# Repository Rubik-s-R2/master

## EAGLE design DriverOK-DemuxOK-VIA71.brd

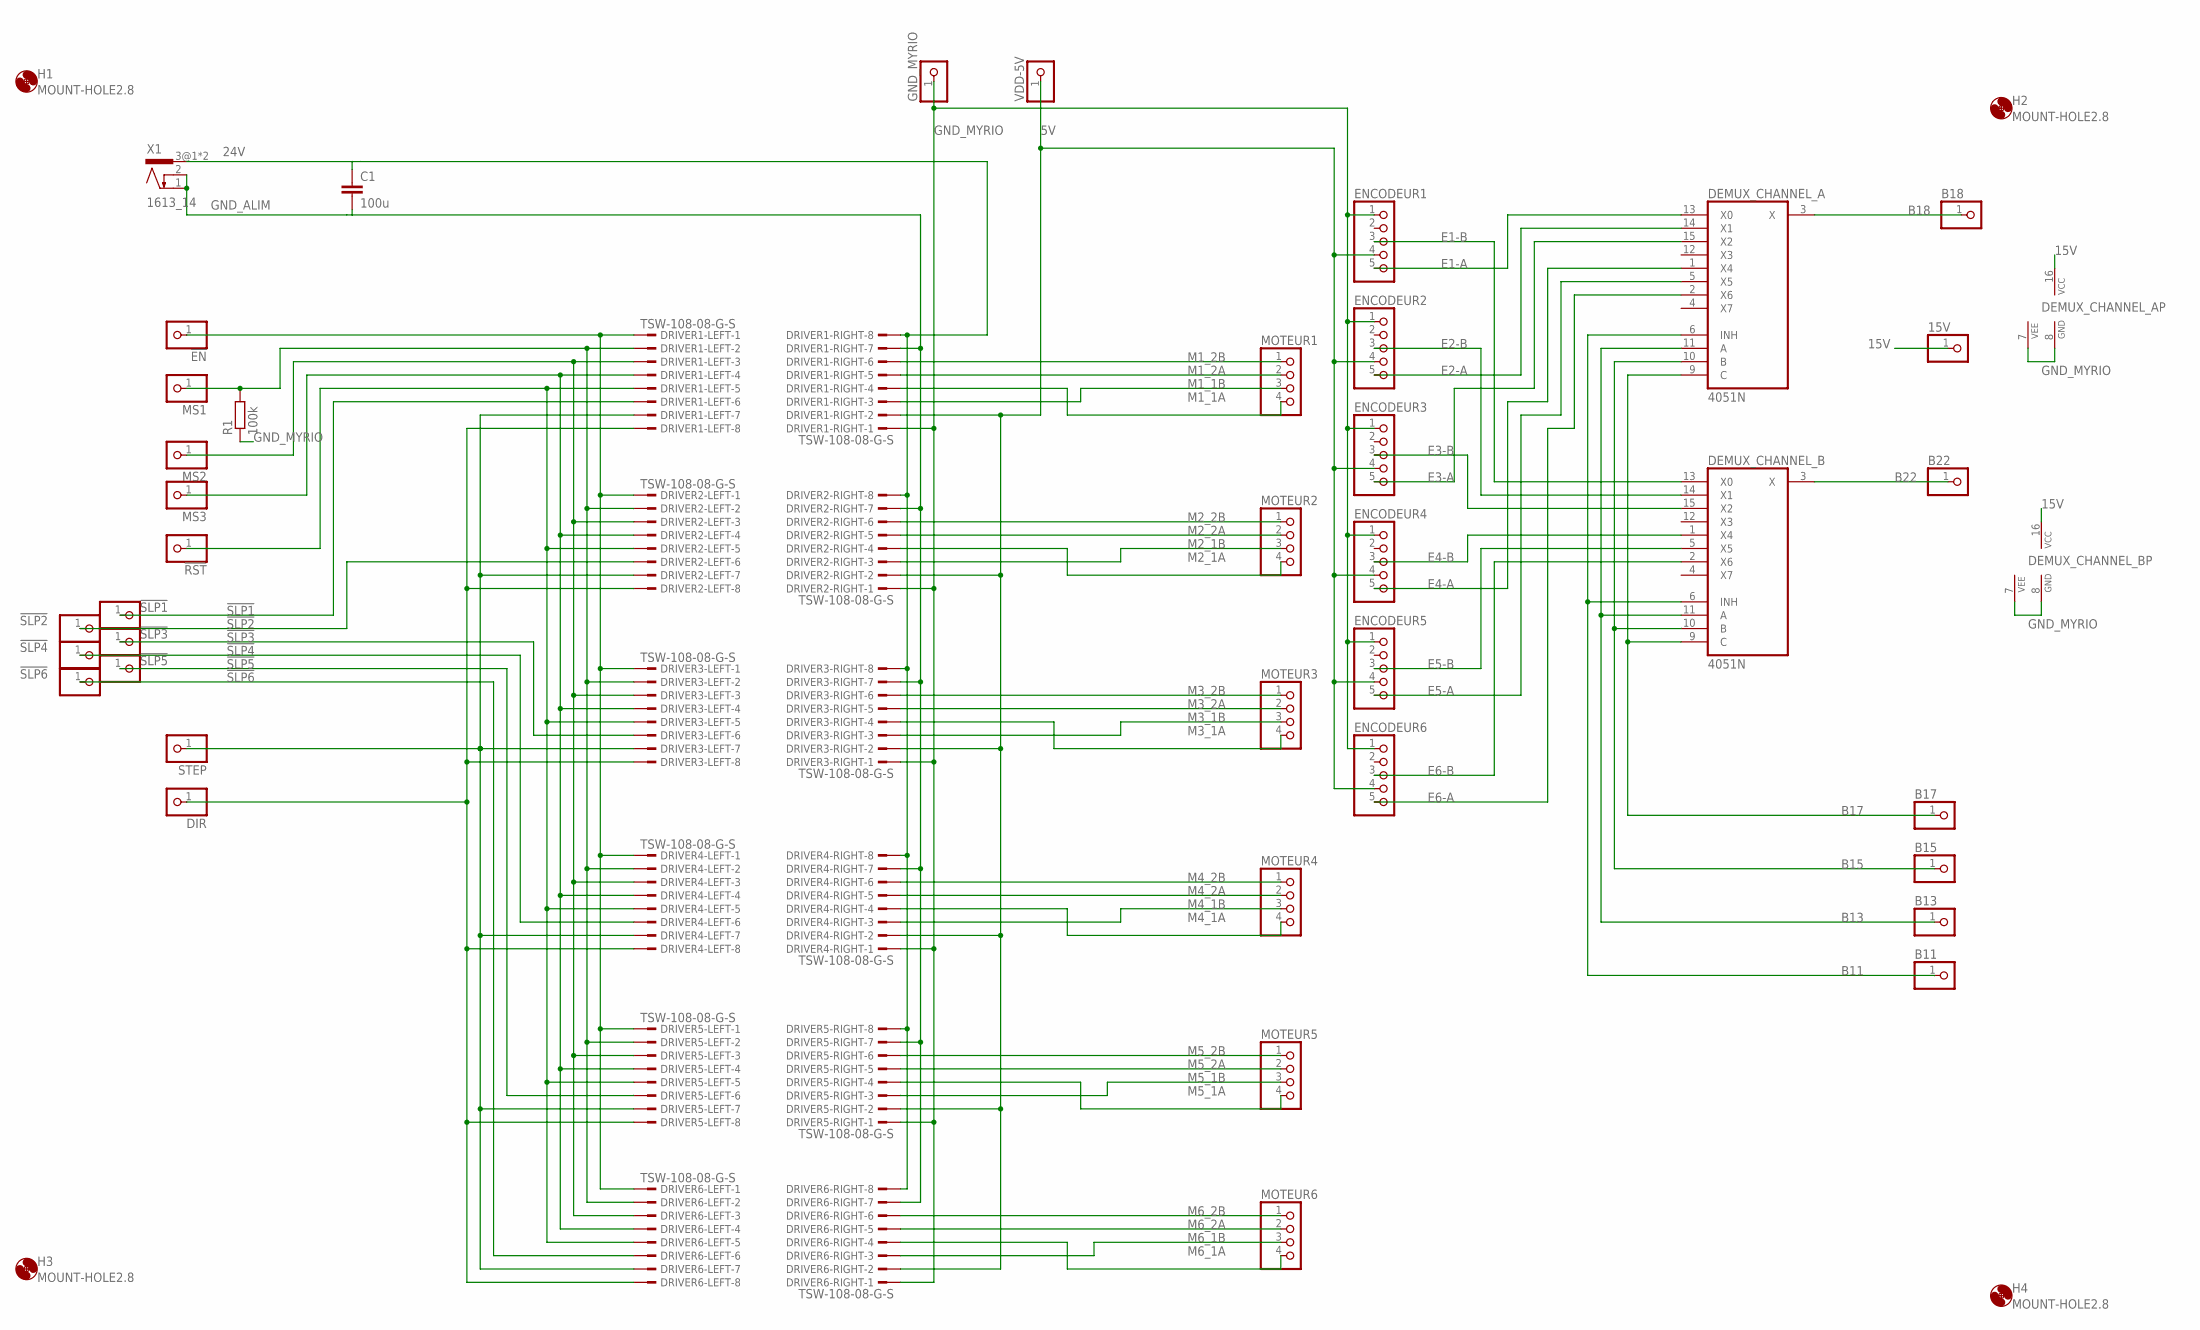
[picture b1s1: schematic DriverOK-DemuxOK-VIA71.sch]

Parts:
15V: PINHD-1X1; 1X01
!EN: PINHD-1X1; 1X01
!RST: PINHD-1X1; 1X01
!SLP1, !SLP2, !SLP3, !SLP4, !SLP5, !SLP6: PINHD-1X1; 1X01
B11, B13, B15, B17, B18, B22: PINHD-1X1; 1X01
C1: 100u; C025-025X050
DEMUX_CHANNEL_A: 4051N; DIL16
DEMUX_CHANNEL_B: 4051N; DIL16
DIR: PINHD-1X1; 1X01
DRIVER1-LEFT, DRIVER1-RIGHT, DRIVER2-LEFT, DRIVER2-RIGHT, DRIVER3-LEFT, DRIVER3-RIGHT, DRIVER4-LEFT, DRIVER4-RIGHT, DRIVER5-LEFT, DRIVER5-RIGHT, DRIVER6-LEFT, DRIVER6-RIGHT: TSW-108-08-G-S; TSW-108-XX-G-S
ENCODEUR1, ENCODEUR2, ENCODEUR3, ENCODEUR4, ENCODEUR5, ENCODEUR6: PINHD-1X5; 1X05
GND_MYRIO: PINHD-1X1; 1X01
H1, H2, H3, H4: MOUNT-HOLE2.8; 2,8
MOTEUR1, MOTEUR2, MOTEUR3, MOTEUR4, MOTEUR5, MOTEUR6: PINHD-1X4; 1X04
MS1, MS2, MS3: PINHD-1X1; 1X01
R1: 100k; 0207/10
STEP: PINHD-1X1; 1X01
VDD-5V: PINHD-1X1; 1X01
X1: 1613_14

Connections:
5V: DRIVER1-RIGHT.2, DRIVER2-RIGHT.2, DRIVER3-RIGHT.2, DRIVER4-RIGHT.2, DRIVER5-RIGHT.2, DRIVER6-RIGHT.2, ENCODEUR1.4, ENCODEUR2.4, ENCODEUR3.4, ENCODEUR4.4, ENCODEUR5.4, ENCODEUR6.4, VDD-5V.1
15V: 15V.1, DEMUX_CHANNEL_A.16 (VCC), DEMUX_CHANNEL_B.16 (VCC)
24V: C1.1, DRIVER1-RIGHT.8, DRIVER2-RIGHT.8, DRIVER3-RIGHT.8, DRIVER4-RIGHT.8, DRIVER5-RIGHT.8, DRIVER6-RIGHT.8, X1.3@1 (3), X1.3@2 (3)
!ENABLE: !EN.1, DRIVER1-LEFT.1, DRIVER2-LEFT.1, DRIVER3-LEFT.1, DRIVER4-LEFT.1, DRIVER5-LEFT.1, DRIVER6-LEFT.1
!RESET: !RST.1, DRIVER1-LEFT.5, DRIVER2-LEFT.5, DRIVER3-LEFT.5, DRIVER4-LEFT.5, DRIVER5-LEFT.5, DRIVER6-LEFT.5
!SLP1: !SLP1.1, DRIVER1-LEFT.6
!SLP2: !SLP2.1, DRIVER2-LEFT.6
!SLP3: !SLP3.1, DRIVER3-LEFT.6
!SLP4: !SLP4.1, DRIVER4-LEFT.6
!SLP5: !SLP5.1, DRIVER5-LEFT.6
!SLP6: !SLP6.1, DRIVER6-LEFT.6
B11: B11.1, DEMUX_CHANNEL_A.6 (INH), DEMUX_CHANNEL_B.6 (INH)
B13: B13.1, DEMUX_CHANNEL_A.11 (A), DEMUX_CHANNEL_B.11 (A)
B15: B15.1, DEMUX_CHANNEL_A.10 (B), DEMUX_CHANNEL_B.10 (B)
B17: B17.1, DEMUX_CHANNEL_A.9 (C), DEMUX_CHANNEL_B.9 (C)
B18: B18.1, DEMUX_CHANNEL_A.3 (X)
B22: B22.1, DEMUX_CHANNEL_B.3 (X)
DIR: DIR.1, DRIVER1-LEFT.8, DRIVER2-LEFT.8, DRIVER3-LEFT.8, DRIVER4-LEFT.8, DRIVER5-LEFT.8, DRIVER6-LEFT.8
E1-A: DEMUX_CHANNEL_A.13 (X0), ENCODEUR1.5
E1-B: DEMUX_CHANNEL_B.13 (X0), ENCODEUR1.3
E2-A: DEMUX_CHANNEL_A.14 (X1), ENCODEUR2.5
E2-B: DEMUX_CHANNEL_B.14 (X1), ENCODEUR2.3
E3-A: DEMUX_CHANNEL_A.15 (X2), ENCODEUR3.5
E3-B: DEMUX_CHANNEL_B.15 (X2), ENCODEUR3.3
E4-A: DEMUX_CHANNEL_A.1 (X4), ENCODEUR4.5
E4-B: DEMUX_CHANNEL_B.1 (X4), ENCODEUR4.3
E5-A: DEMUX_CHANNEL_A.5 (X5), ENCODEUR5.5
E5-B: DEMUX_CHANNEL_B.5 (X5), ENCODEUR5.3
E6-A: DEMUX_CHANNEL_A.2 (X6), ENCODEUR6.5
E6-B: DEMUX_CHANNEL_B.2 (X6), ENCODEUR6.3
GND_ALIM: C1.2, DRIVER1-RIGHT.7, DRIVER2-RIGHT.7, DRIVER3-RIGHT.7, DRIVER4-RIGHT.7, DRIVER5-RIGHT.7, DRIVER6-RIGHT.7, X1.1, X1.2
GND_MYRIO: DEMUX_CHANNEL_A.7 (VEE), DEMUX_CHANNEL_A.8 (GND), DEMUX_CHANNEL_B.7 (VEE), DEMUX_CHANNEL_B.8 (GND), DRIVER1-RIGHT.1, DRIVER2-RIGHT.1, DRIVER3-RIGHT.1, DRIVER4-RIGHT.1, DRIVER5-RIGHT.1, DRIVER6-RIGHT.1, ENCODEUR1.1, ENCODEUR2.1, ENCODEUR3.1, ENCODEUR4.1, ENCODEUR5.1, ENCODEUR6.1, GND_MYRIO.1, R1.1
M1_1A: DRIVER1-RIGHT.4, MOTEUR1.4
M1_1B: DRIVER1-RIGHT.3, MOTEUR1.3
M1_2A: DRIVER1-RIGHT.5, MOTEUR1.2
M1_2B: DRIVER1-RIGHT.6, MOTEUR1.1
M2_1A: DRIVER2-RIGHT.4, MOTEUR2.4
M2_1B: DRIVER2-RIGHT.3, MOTEUR2.3
M2_2A: DRIVER2-RIGHT.5, MOTEUR2.2
M2_2B: DRIVER2-RIGHT.6, MOTEUR2.1
M3_1A: DRIVER3-RIGHT.4, MOTEUR3.4
M3_1B: DRIVER3-RIGHT.3, MOTEUR3.3
M3_2A: DRIVER3-RIGHT.5, MOTEUR3.2
M3_2B: DRIVER3-RIGHT.6, MOTEUR3.1
M4_1A: DRIVER4-RIGHT.4, MOTEUR4.4
M4_1B: DRIVER4-RIGHT.3, MOTEUR4.3
M4_2A: DRIVER4-RIGHT.5, MOTEUR4.2
M4_2B: DRIVER4-RIGHT.6, MOTEUR4.1
M5_1A: DRIVER5-RIGHT.4, MOTEUR5.4
M5_1B: DRIVER5-RIGHT.3, MOTEUR5.3
M5_2A: DRIVER5-RIGHT.5, MOTEUR5.2
M5_2B: DRIVER5-RIGHT.6, MOTEUR5.1
M6_1A: DRIVER6-RIGHT.4, MOTEUR6.4
M6_1B: DRIVER6-RIGHT.3, MOTEUR6.3
M6_2A: DRIVER6-RIGHT.5, MOTEUR6.2
M6_2B: DRIVER6-RIGHT.6, MOTEUR6.1
MS1: DRIVER1-LEFT.2, DRIVER2-LEFT.2, DRIVER3-LEFT.2, DRIVER4-LEFT.2, DRIVER5-LEFT.2, DRIVER6-LEFT.2, MS1.1, R1.2
MS2: DRIVER1-LEFT.3, DRIVER2-LEFT.3, DRIVER3-LEFT.3, DRIVER4-LEFT.3, DRIVER5-LEFT.3, DRIVER6-LEFT.3, MS2.1
MS3: DRIVER1-LEFT.4, DRIVER2-LEFT.4, DRIVER3-LEFT.4, DRIVER4-LEFT.4, DRIVER5-LEFT.4, DRIVER6-LEFT.4, MS3.1
STEP: DRIVER1-LEFT.7, DRIVER2-LEFT.7, DRIVER3-LEFT.7, DRIVER4-LEFT.7, DRIVER5-LEFT.7, DRIVER6-LEFT.7, STEP.1

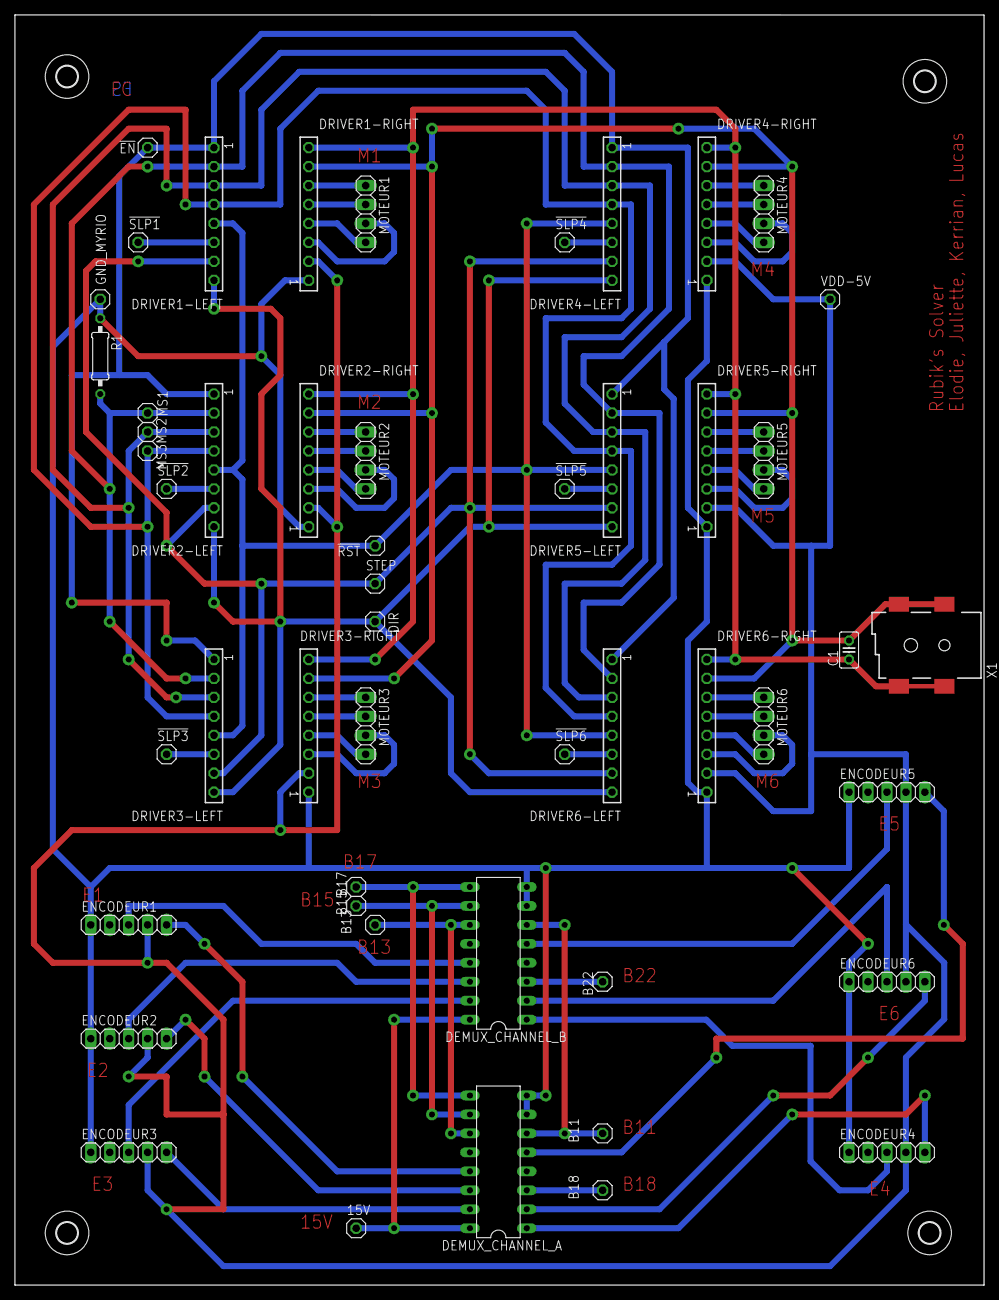
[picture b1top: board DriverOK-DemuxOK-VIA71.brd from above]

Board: 2 copper layers, 129.8 x 170.2 mm, 55 parts (0 on the bottom side), 60 nets.

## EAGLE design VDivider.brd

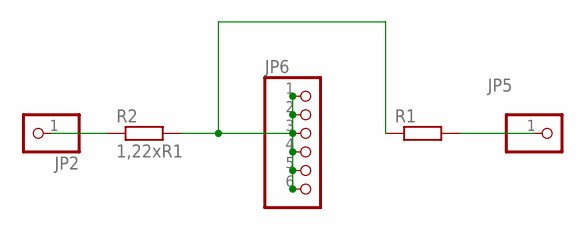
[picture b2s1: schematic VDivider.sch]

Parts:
JP2, JP5: PINHD-1X1; 1X01
JP6: PINHD-1X6; 1X06
R1: R-EU_0204/7; 0204/7
R2: 1,22xR1; 0204/7

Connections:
unnamed: JP2.1, R2.1
unnamed: JP6.1, JP6.2, JP6.3, JP6.4, JP6.5, JP6.6, R1.1, R2.2
unnamed: JP5.1, R1.2

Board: 2 copper layers, 5 parts (0 on the bottom side), 3 nets, no tracks yet.

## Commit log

2021-04-12 Test
2021-04-12 Solidworks 12/04
2021-04-13 Ajout de la deuxième version de la modélisation du pied
2021-04-14 Modelisation of the case holder for the camera and its support allowing rotation along one axis
2021-04-14 Folder for solidworks modelisations
2021-04-14 Modelisations of 3D pieces for the system
2021-04-14 Congés sur la case
2021-04-14 Update modelisation
2021-04-15 Modification de la longueur de la pièce
2021-04-15 Modification rayon ouverture vers cube
2021-04-16 Elargissement fourreau arbre moteur
2021-04-16 traitement cam A1 1.0
2021-04-16 traitement cam A1
2021-04-16 Dessin des cartes électroniques Driver et myRIO
2021-04-19 Encodeurs>Demux>myRIO
2021-04-19 Ajout de pinhead pour le pont diviseur de tension
2021-04-21 Add files via upload
    version avec ROI + coordonnées tab init
2021-04-22 Complete Board and schematics on EAGLE, drivers, demux and 24V source
2021-04-22 Added AlgorithmeResolution.drawio
2021-04-22 Deletion of an extra draw.io
2021-04-22 Update board and schematics
2021-04-22 Suppresion du pont diviseur
2021-04-23 Cablage alternatif pour la carte, avec moins de via ici
2021-04-27 EAGLE board and schematics
    Changement du placement et des branchements pour réduire le nombre de via
2021-04-27 Update largeur de la board
2021-04-30 Suppression de fichiers doublons (EAGLE board etc.) après l'élaboration de la version finale de la carte
2021-05-19 Deletion of previous version of plugs
2021-05-27 Capture du Vi principal
2021-05-27 Capture of sub-Vis
2021-05-27 Draw.io s
2021-05-27 Full project
2021-05-27 Resoluytion
2021-05-27 Rubik's Solver
2021-05-27 Datasheets
2021-05-27 Rangement
2021-05-28 solidwo
2021-05-28 enco
2021-05-28 moteur
2021-05-28 capture
2021-05-28 gsfs
